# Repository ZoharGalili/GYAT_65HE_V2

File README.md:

# GYAT_65HE_V2
65% hall effect keyboard

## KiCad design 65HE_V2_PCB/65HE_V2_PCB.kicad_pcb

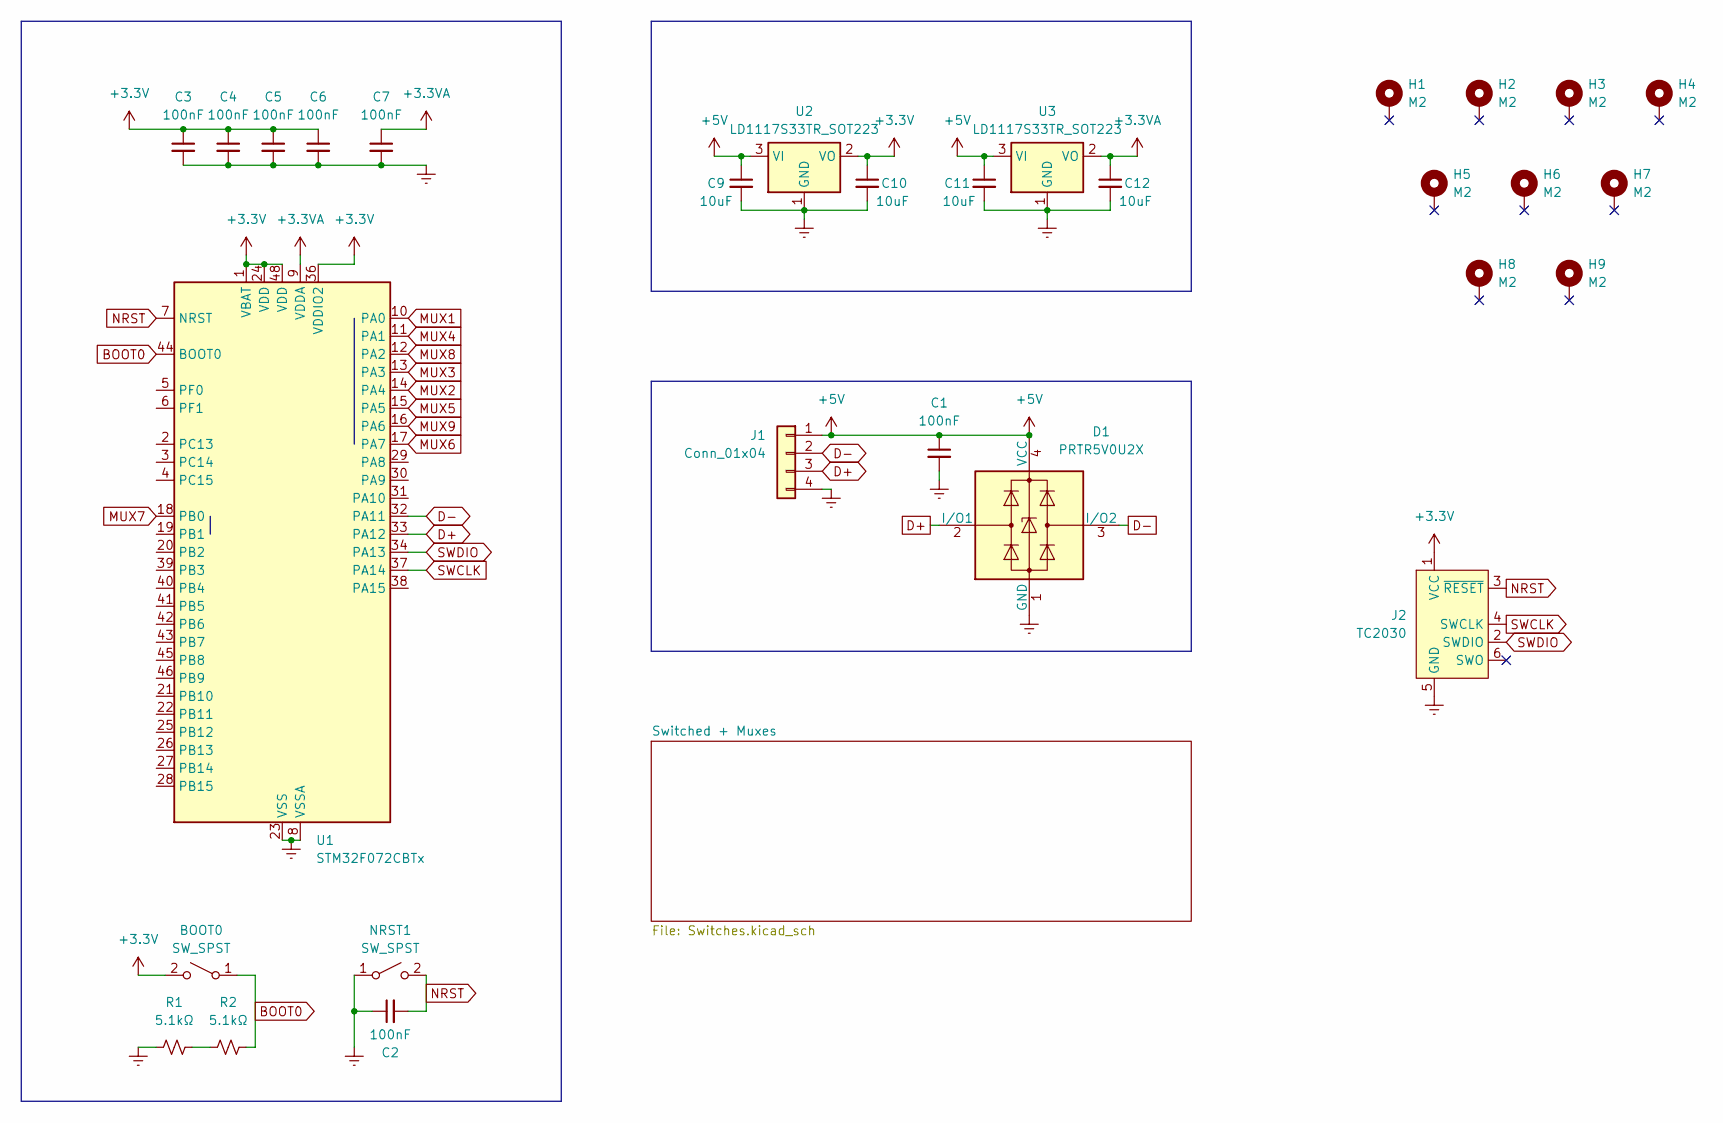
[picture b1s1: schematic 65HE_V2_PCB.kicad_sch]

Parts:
BOOT0: SW_SPST; SW_MSK12C02-HB
C1, C2, C3, C4, C5, C6, C7: 100nF; C_0805_2012Metric
C9, C10, C11, C12: 10uF; C_1206_3216Metric
D1: PRTR5V0U2X; SOT-143
H1, H2, H3, H4, H5, H6, H7, H8, H9: M2; MountingHole_2.2mm_M2_Pad
J1: Conn_01x04; JST_SH_SM04B-SRSS-TB_1x04-1MP_P1.00mm_Horizontal
J2: TC2030; Tag-Connect_TC2030-IDC-FP_2x03_P1.27mm_Vertical
NRST1: SW_SPST; SW_SPST_SKQG_WithStem
R1, R2: 5.1kΩ; R_0805_2012Metric
U1: STM32F072CBTx; LQFP-48_7x7mm_P0.5mm
U2, U3: LD1117S33TR_SOT223; SOT-223-3_TabPin2; LCSC C71121

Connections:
+3.3V: BOOT0.2 (B), C3.1, C4.1, C5.1, C6.1, C10.1, J2.1 (VCC), U1.1 (VBAT), U1.24 (VDD), U1.36 (VDDIO2), U1.48 (VDD), U2.2 (VO); also elsewhere on the board
+3.3VA: C7.1, C12.1, U1.9 (VDDA), U3.2 (VO); also elsewhere on the board
+5V: C1.1, C9.1, C11.1, D1.4 (VCC), J1.1, U2.3 (VI), U3.3 (VI); also elsewhere on the board
BOOT0: BOOT0.1 (A), R2.2, U1.44 (BOOT0); also elsewhere on the board
D+: D1.2 (I/O1), J1.3, U1.33 (PA12); also elsewhere on the board
D-: D1.3 (I/O2), J1.2, U1.32 (PA11); also elsewhere on the board
Earth: C1.2, C2.1, C3.2, C4.2, C5.2, C6.2, C7.2, C9.2, C10.2, C11.2, C12.2, D1.1 (GND), J1.4, J2.5 (GND), NRST1.1 (A), R1.1, U1.8 (VSSA), U1.23 (VSS), U1.35 (VSS), U1.47 (VSS), U2.1 (GND), U3.1 (GND); also elsewhere on the board
MUX1: U1.10 (PA0); also elsewhere on the board
MUX2: U1.14 (PA4); also elsewhere on the board
MUX3: U1.13 (PA3); also elsewhere on the board
MUX4: U1.11 (PA1); also elsewhere on the board
MUX5: U1.15 (PA5); also elsewhere on the board
MUX6: U1.17 (PA7); also elsewhere on the board
MUX7: U1.18 (PB0); also elsewhere on the board
MUX8: U1.12 (PA2); also elsewhere on the board
MUX9: U1.16 (PA6); also elsewhere on the board
NRST: C2.2, J2.3 (~RESET), NRST1.2 (B), U1.7 (NRST); also elsewhere on the board
unnamed: R1.2, R2.1
SWCLK: J2.4 (SWCLK), U1.37 (PA14); also elsewhere on the board
SWDIO: J2.2 (SWDIO), U1.34 (PA13); also elsewhere on the board

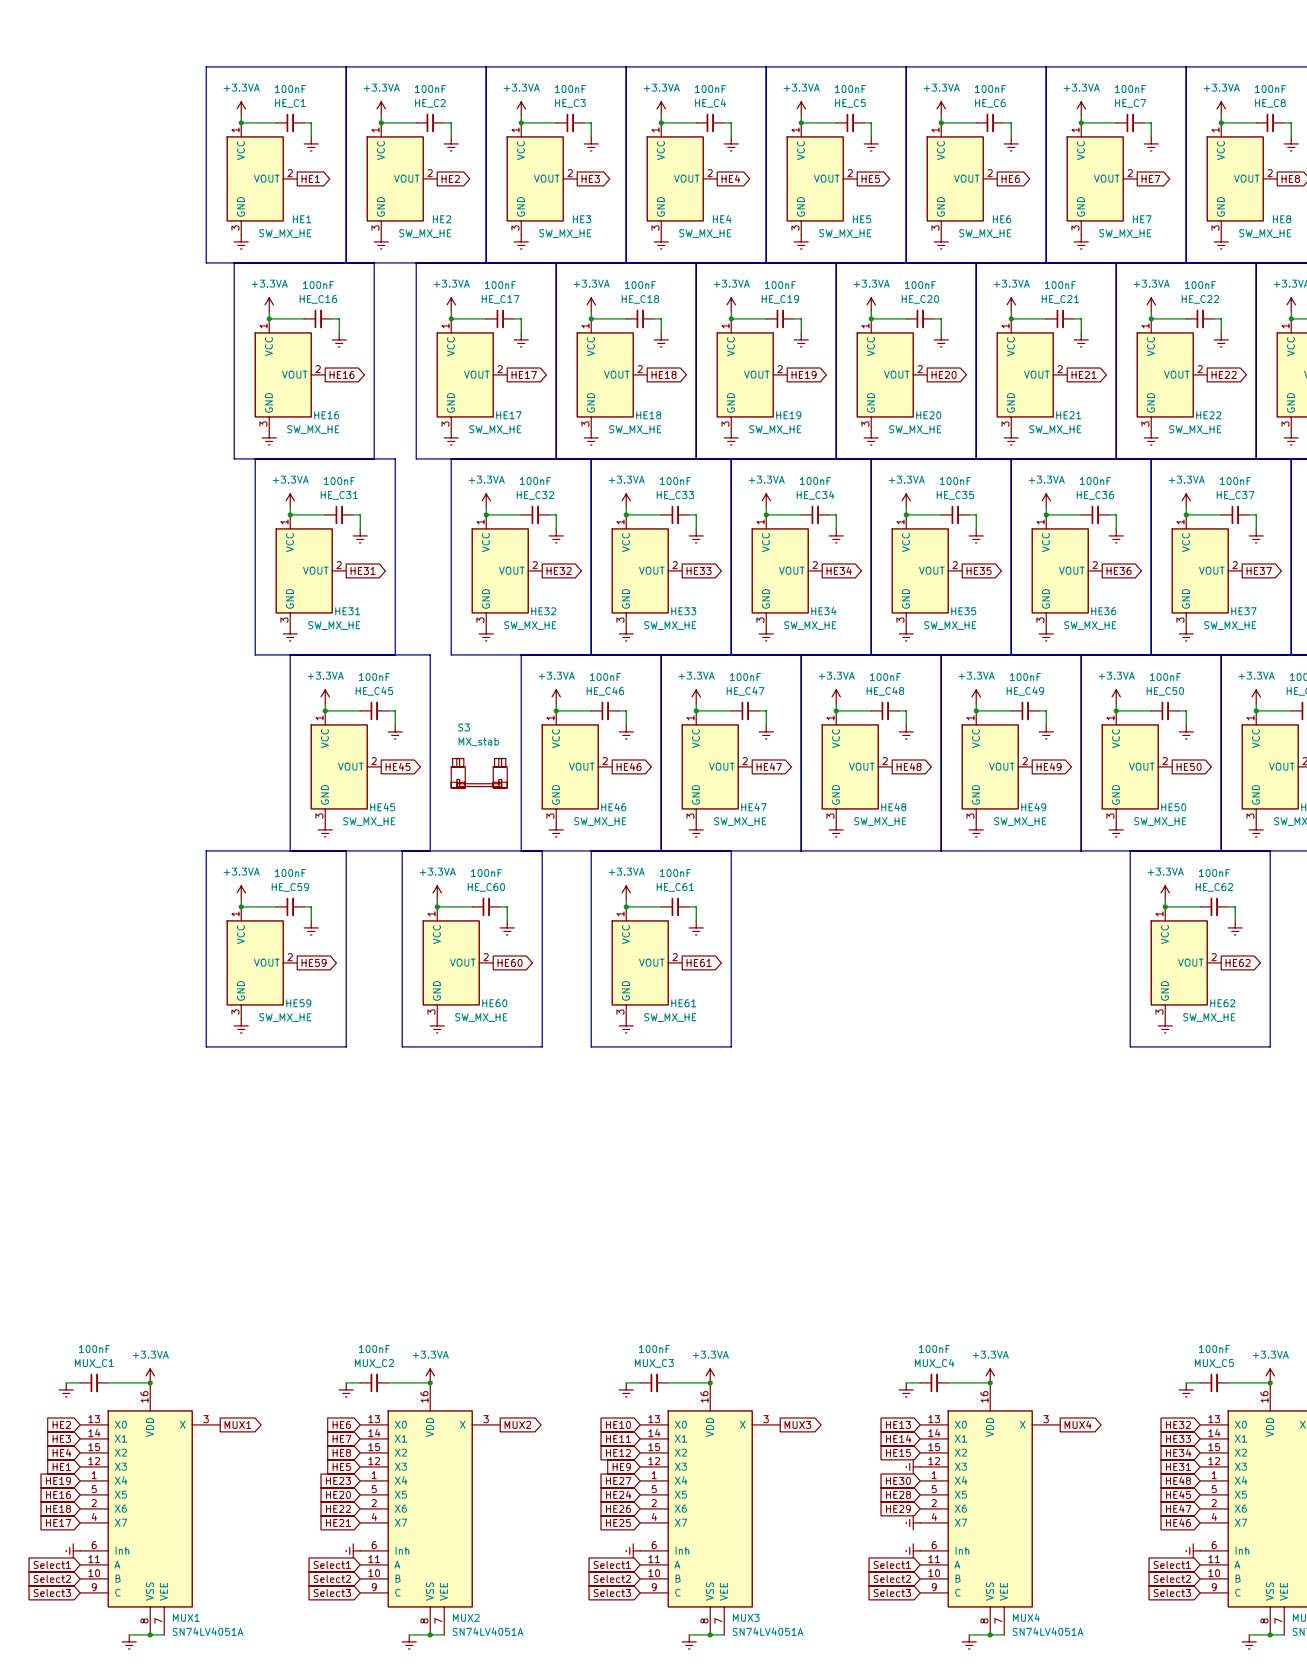
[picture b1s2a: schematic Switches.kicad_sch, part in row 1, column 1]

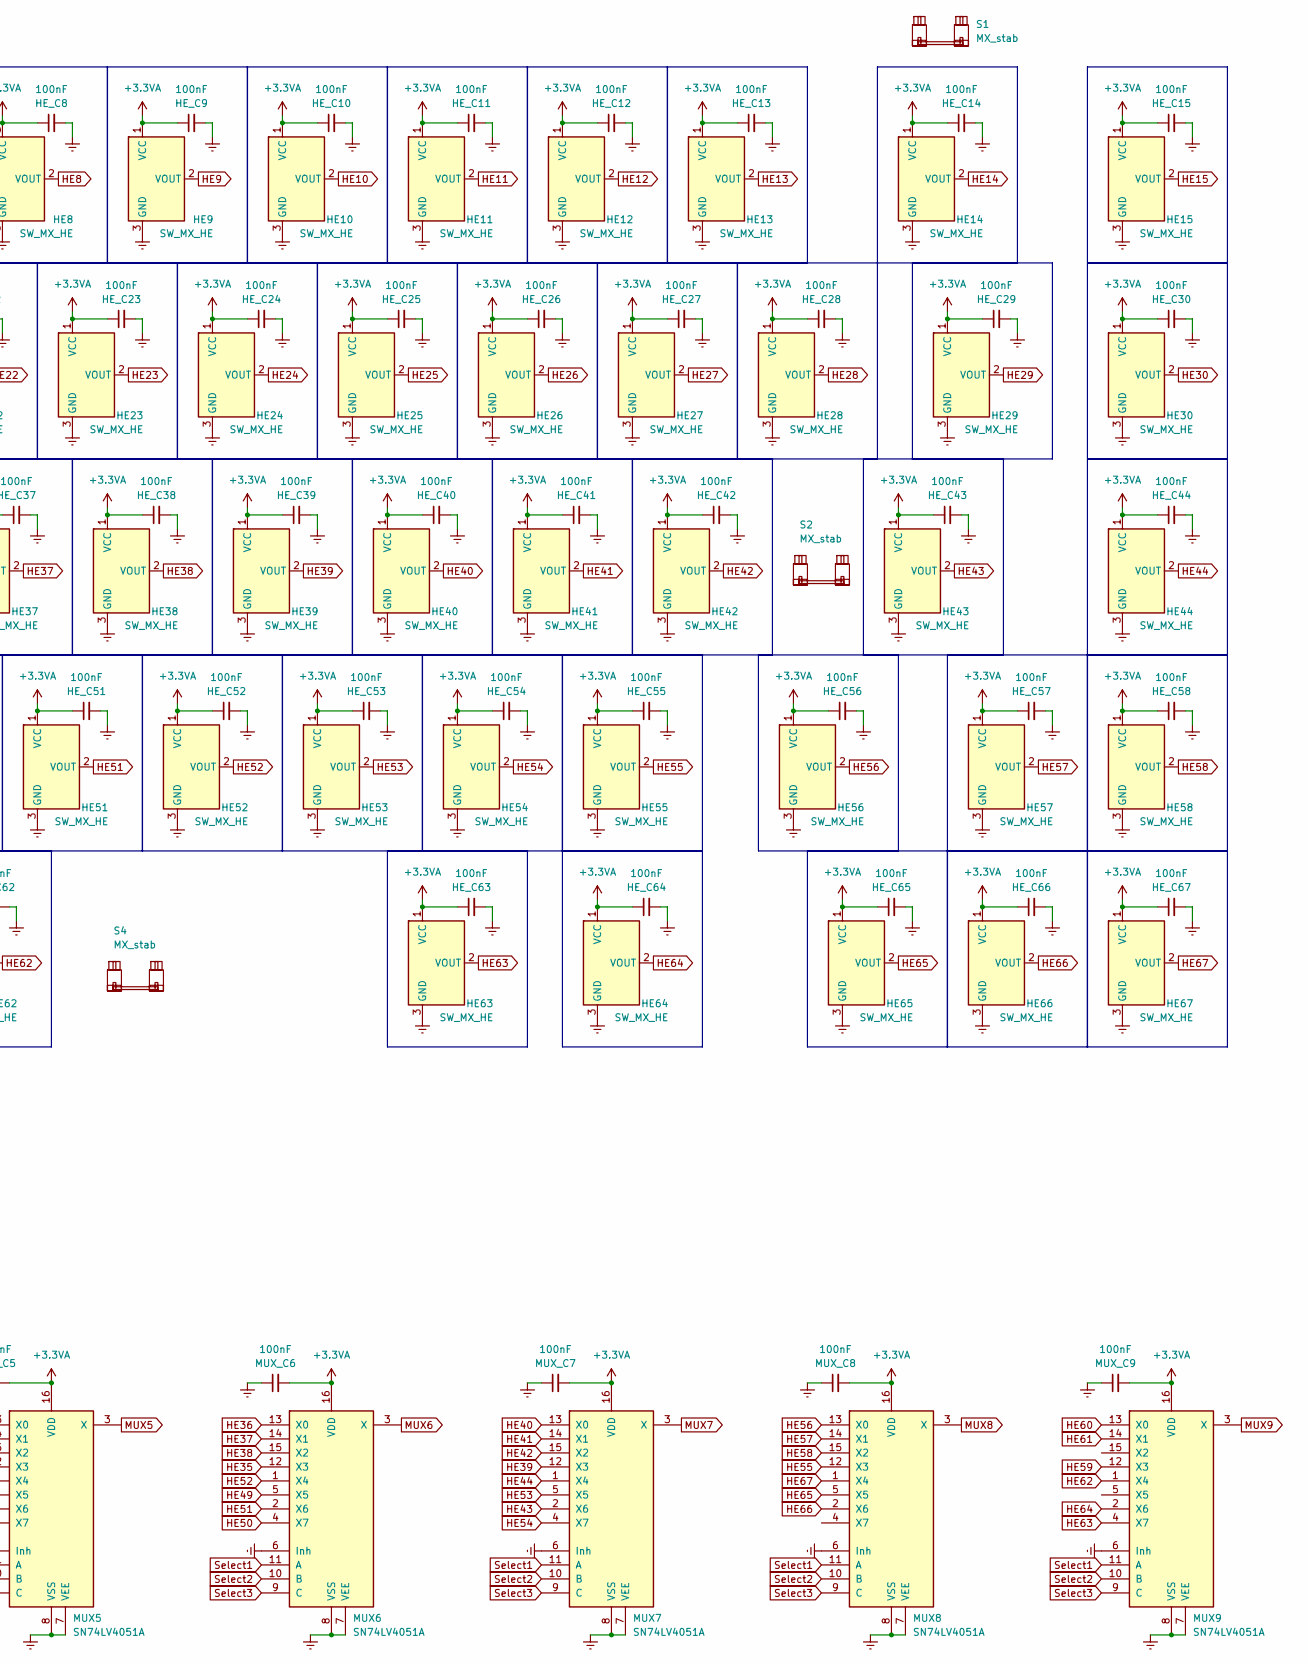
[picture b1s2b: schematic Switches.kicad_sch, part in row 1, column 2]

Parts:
HE1, HE2, HE3, HE4, HE5, HE6, HE7, HE8, HE9, HE10, HE11, HE12, HE13, HE14, HE15, HE16, HE17, HE18, HE19, HE20, HE21, HE22, HE23, HE24, HE25, HE26, HE27, HE28, HE29, HE30, HE31, HE32, HE33, HE34, HE35, HE36, HE37, HE38, HE39, HE40, HE41, HE42, HE43, HE44, HE45, HE46, HE47, HE48, HE49, HE50, HE51, HE52, HE53, HE54, HE55, HE56, HE57, HE58, HE59, HE60, HE61, HE62, HE63, HE64, HE65, HE66, HE67: SW_MX_HE; SW_MX_HE_90deg_1u
HE_C1, HE_C2, HE_C3, HE_C4, HE_C5, HE_C6, HE_C7, HE_C8, HE_C9, HE_C10, HE_C11, HE_C12, HE_C13, HE_C14, HE_C15, HE_C16, HE_C17, HE_C18, HE_C19, HE_C20, HE_C21, HE_C22, HE_C23, HE_C24, HE_C25, HE_C26, HE_C27, HE_C28, HE_C29, HE_C30, HE_C31, HE_C32, HE_C33, HE_C34, HE_C35, HE_C36, HE_C37, HE_C38, HE_C39, HE_C40, HE_C41, HE_C42, HE_C43, HE_C44, HE_C45, HE_C46, HE_C47, HE_C48, HE_C49, HE_C50, HE_C51, HE_C52, HE_C53, HE_C54, HE_C55, HE_C56, HE_C57, HE_C58, HE_C59, HE_C60, HE_C61, HE_C62, HE_C63, HE_C64, HE_C65, HE_C66, HE_C67: 100nF; C_0805_2012Metric
MUX1, MUX2, MUX3, MUX4, MUX5, MUX6, MUX7, MUX8, MUX9: SN74LV4051A; TSSOP-16_4.4x5mm_P0.65mm
MUX_C1, MUX_C2, MUX_C3, MUX_C4, MUX_C5, MUX_C6, MUX_C7, MUX_C8, MUX_C9: 100nF; C_0805_2012Metric
S1: MX_stab; STAB_MX_2u
S2, S3: MX_stab; STAB_MX_2.25u
S4: MX_stab; STAB_MX_6.25u

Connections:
+3.3VA: HE1.1 (VCC), HE2.1 (VCC), HE3.1 (VCC), HE4.1 (VCC), HE5.1 (VCC), HE6.1 (VCC), HE7.1 (VCC), HE8.1 (VCC), HE9.1 (VCC), HE10.1 (VCC), HE11.1 (VCC), HE12.1 (VCC), HE13.1 (VCC), HE14.1 (VCC), HE15.1 (VCC), HE16.1 (VCC), HE17.1 (VCC), HE18.1 (VCC), HE19.1 (VCC), HE20.1 (VCC), HE21.1 (VCC), HE22.1 (VCC), HE23.1 (VCC), HE24.1 (VCC), HE25.1 (VCC), HE26.1 (VCC), HE27.1 (VCC), HE28.1 (VCC), HE29.1 (VCC), HE30.1 (VCC), HE31.1 (VCC), HE32.1 (VCC), HE33.1 (VCC), HE34.1 (VCC), HE35.1 (VCC), HE36.1 (VCC), HE37.1 (VCC), HE38.1 (VCC), HE39.1 (VCC), HE40.1 (VCC), HE41.1 (VCC), HE42.1 (VCC), HE43.1 (VCC), HE44.1 (VCC), HE45.1 (VCC), HE46.1 (VCC), HE47.1 (VCC), HE48.1 (VCC), HE49.1 (VCC), HE50.1 (VCC), HE51.1 (VCC), HE52.1 (VCC), HE53.1 (VCC), HE54.1 (VCC), HE55.1 (VCC), HE56.1 (VCC), HE57.1 (VCC), HE58.1 (VCC), HE59.1 (VCC), HE60.1 (VCC), HE61.1 (VCC), HE62.1 (VCC), HE63.1 (VCC), HE64.1 (VCC), HE65.1 (VCC), HE66.1 (VCC), HE67.1 (VCC), HE_C1.1, HE_C2.1, HE_C3.1, HE_C4.1, HE_C5.1, HE_C6.1, HE_C7.1, HE_C8.1, HE_C9.1, HE_C10.1, HE_C11.1, HE_C12.1, HE_C13.1, HE_C14.1, HE_C15.1, HE_C16.1, HE_C17.1, HE_C18.1, HE_C19.1, HE_C20.1, HE_C21.1, HE_C22.1, HE_C23.1, HE_C24.1, HE_C25.1, HE_C26.1, HE_C27.1, HE_C28.1, HE_C29.1, HE_C30.1, HE_C31.1, HE_C32.1, HE_C33.1, HE_C34.1, HE_C35.1, HE_C36.1, HE_C37.1, HE_C38.1, HE_C39.1, HE_C40.1, HE_C41.1, HE_C42.1, HE_C43.1, HE_C44.1, HE_C45.1, HE_C46.1, HE_C47.1, HE_C48.1, HE_C49.1, HE_C50.1, HE_C51.1, HE_C52.1, HE_C53.1, HE_C54.1, HE_C55.1, HE_C56.1, HE_C57.1, HE_C58.1, HE_C59.1, HE_C60.1, HE_C61.1, HE_C62.1, HE_C63.1, HE_C64.1, HE_C65.1, HE_C66.1, HE_C67.1, MUX1.16 (VDD), MUX2.16 (VDD), MUX3.16 (VDD), MUX4.16 (VDD), MUX5.16 (VDD), MUX6.16 (VDD), MUX7.16 (VDD), MUX8.16 (VDD), MUX9.16 (VDD), MUX_C1.2, MUX_C2.2, MUX_C3.2, MUX_C4.2, MUX_C5.2, MUX_C6.2, MUX_C7.2, MUX_C8.2, MUX_C9.2; also elsewhere on the board
Earth: HE1.3 (GND), HE2.3 (GND), HE3.3 (GND), HE4.3 (GND), HE5.3 (GND), HE6.3 (GND), HE7.3 (GND), HE8.3 (GND), HE9.3 (GND), HE10.3 (GND), HE11.3 (GND), HE12.3 (GND), HE13.3 (GND), HE14.3 (GND), HE15.3 (GND), HE16.3 (GND), HE17.3 (GND), HE18.3 (GND), HE19.3 (GND), HE20.3 (GND), HE21.3 (GND), HE22.3 (GND), HE23.3 (GND), HE24.3 (GND), HE25.3 (GND), HE26.3 (GND), HE27.3 (GND), HE28.3 (GND), HE29.3 (GND), HE30.3 (GND), HE31.3 (GND), HE32.3 (GND), HE33.3 (GND), HE34.3 (GND), HE35.3 (GND), HE36.3 (GND), HE37.3 (GND), HE38.3 (GND), HE39.3 (GND), HE40.3 (GND), HE41.3 (GND), HE42.3 (GND), HE43.3 (GND), HE44.3 (GND), HE45.3 (GND), HE46.3 (GND), HE47.3 (GND), HE48.3 (GND), HE49.3 (GND), HE50.3 (GND), HE51.3 (GND), HE52.3 (GND), HE53.3 (GND), HE54.3 (GND), HE55.3 (GND), HE56.3 (GND), HE57.3 (GND), HE58.3 (GND), HE59.3 (GND), HE60.3 (GND), HE61.3 (GND), HE62.3 (GND), HE63.3 (GND), HE64.3 (GND), HE65.3 (GND), HE66.3 (GND), HE67.3 (GND), HE_C1.2, HE_C2.2, HE_C3.2, HE_C4.2, HE_C5.2, HE_C6.2, HE_C7.2, HE_C8.2, HE_C9.2, HE_C10.2, HE_C11.2, HE_C12.2, HE_C13.2, HE_C14.2, HE_C15.2, HE_C16.2, HE_C17.2, HE_C18.2, HE_C19.2, HE_C20.2, HE_C21.2, HE_C22.2, HE_C23.2, HE_C24.2, HE_C25.2, HE_C26.2, HE_C27.2, HE_C28.2, HE_C29.2, HE_C30.2, HE_C31.2, HE_C32.2, HE_C33.2, HE_C34.2, HE_C35.2, HE_C36.2, HE_C37.2, HE_C38.2, HE_C39.2, HE_C40.2, HE_C41.2, HE_C42.2, HE_C43.2, HE_C44.2, HE_C45.2, HE_C46.2, HE_C47.2, HE_C48.2, HE_C49.2, HE_C50.2, HE_C51.2, HE_C52.2, HE_C53.2, HE_C54.2, HE_C55.2, HE_C56.2, HE_C57.2, HE_C58.2, HE_C59.2, HE_C60.2, HE_C61.2, HE_C62.2, HE_C63.2, HE_C64.2, HE_C65.2, HE_C66.2, HE_C67.2, MUX1.6 (Inh), MUX1.7 (VEE), MUX1.8 (VSS), MUX2.6 (Inh), MUX2.7 (VEE), MUX2.8 (VSS), MUX3.6 (Inh), MUX3.7 (VEE), MUX3.8 (VSS), MUX4.4 (X7), MUX4.6 (Inh), MUX4.7 (VEE), MUX4.8 (VSS), MUX4.12 (X3), MUX5.6 (Inh), MUX5.7 (VEE), MUX5.8 (VSS), MUX6.6 (Inh), MUX6.7 (VEE), MUX6.8 (VSS), MUX7.6 (Inh), MUX7.7 (VEE), MUX7.8 (VSS), MUX8.6 (Inh), MUX8.7 (VEE), MUX8.8 (VSS), MUX9.6 (Inh), MUX9.7 (VEE), MUX9.8 (VSS), MUX_C1.1, MUX_C2.1, MUX_C3.1, MUX_C4.1, MUX_C5.1, MUX_C6.1, MUX_C7.1, MUX_C8.1, MUX_C9.1; also elsewhere on the board
HE1: HE1.2 (VOUT), MUX1.12 (X3)
HE2: HE2.2 (VOUT), MUX1.13 (X0)
HE3: HE3.2 (VOUT), MUX1.14 (X1)
HE4: HE4.2 (VOUT), MUX1.15 (X2)
HE5: HE5.2 (VOUT), MUX2.12 (X3)
HE6: HE6.2 (VOUT), MUX2.13 (X0)
HE7: HE7.2 (VOUT), MUX2.14 (X1)
HE8: HE8.2 (VOUT), MUX2.15 (X2)
HE9: HE9.2 (VOUT), MUX3.12 (X3)
HE10: HE10.2 (VOUT), MUX3.13 (X0)
HE11: HE11.2 (VOUT), MUX3.14 (X1)
HE12: HE12.2 (VOUT), MUX3.15 (X2)
HE13: HE13.2 (VOUT), MUX4.13 (X0)
HE14: HE14.2 (VOUT), MUX4.14 (X1)
HE15: HE15.2 (VOUT), MUX4.15 (X2)
HE16: HE16.2 (VOUT), MUX1.5 (X5)
HE17: HE17.2 (VOUT), MUX1.4 (X7)
HE18: HE18.2 (VOUT), MUX1.2 (X6)
HE19: HE19.2 (VOUT), MUX1.1 (X4)
HE20: HE20.2 (VOUT), MUX2.5 (X5)
HE21: HE21.2 (VOUT), MUX2.4 (X7)
HE22: HE22.2 (VOUT), MUX2.2 (X6)
HE23: HE23.2 (VOUT), MUX2.1 (X4)
HE24: HE24.2 (VOUT), MUX3.5 (X5)
HE25: HE25.2 (VOUT), MUX3.4 (X7)
HE26: HE26.2 (VOUT), MUX3.2 (X6)
HE27: HE27.2 (VOUT), MUX3.1 (X4)
HE28: HE28.2 (VOUT), MUX4.5 (X5)
HE29: HE29.2 (VOUT), MUX4.2 (X6)
HE30: HE30.2 (VOUT), MUX4.1 (X4)
HE31: HE31.2 (VOUT), MUX5.12 (X3)
HE32: HE32.2 (VOUT), MUX5.13 (X0)
HE33: HE33.2 (VOUT), MUX5.14 (X1)
HE34: HE34.2 (VOUT), MUX5.15 (X2)
HE35: HE35.2 (VOUT), MUX6.12 (X3)
HE36: HE36.2 (VOUT), MUX6.13 (X0)
HE37: HE37.2 (VOUT), MUX6.14 (X1)
HE38: HE38.2 (VOUT), MUX6.15 (X2)
HE39: HE39.2 (VOUT), MUX7.12 (X3)
HE40: HE40.2 (VOUT), MUX7.13 (X0)
HE41: HE41.2 (VOUT), MUX7.14 (X1)
HE42: HE42.2 (VOUT), MUX7.15 (X2)
HE43: HE43.2 (VOUT), MUX7.2 (X6)
HE44: HE44.2 (VOUT), MUX7.1 (X4)
HE45: HE45.2 (VOUT), MUX5.5 (X5)
HE46: HE46.2 (VOUT), MUX5.4 (X7)
HE47: HE47.2 (VOUT), MUX5.2 (X6)
HE48: HE48.2 (VOUT), MUX5.1 (X4)
HE49: HE49.2 (VOUT), MUX6.5 (X5)
HE50: HE50.2 (VOUT), MUX6.4 (X7)
HE51: HE51.2 (VOUT), MUX6.2 (X6)
HE52: HE52.2 (VOUT), MUX6.1 (X4)
HE53: HE53.2 (VOUT), MUX7.5 (X5)
HE54: HE54.2 (VOUT), MUX7.4 (X7)
HE55: HE55.2 (VOUT), MUX8.12 (X3)
HE56: HE56.2 (VOUT), MUX8.13 (X0)
HE57: HE57.2 (VOUT), MUX8.14 (X1)
HE58: HE58.2 (VOUT), MUX8.15 (X2)
HE59: HE59.2 (VOUT), MUX9.12 (X3)
HE60: HE60.2 (VOUT), MUX9.13 (X0)
HE61: HE61.2 (VOUT), MUX9.14 (X1)
HE62: HE62.2 (VOUT), MUX9.1 (X4)
HE63: HE63.2 (VOUT), MUX9.4 (X7)
HE64: HE64.2 (VOUT), MUX9.2 (X6)
HE65: HE65.2 (VOUT), MUX8.5 (X5)
HE66: HE66.2 (VOUT), MUX8.2 (X6)
HE67: HE67.2 (VOUT), MUX8.1 (X4)
MUX1: MUX1.3 (X); also elsewhere on the board
MUX2: MUX2.3 (X); also elsewhere on the board
MUX3: MUX3.3 (X); also elsewhere on the board
MUX4: MUX4.3 (X); also elsewhere on the board
MUX5: MUX5.3 (X); also elsewhere on the board
MUX6: MUX6.3 (X); also elsewhere on the board
MUX7: MUX7.3 (X); also elsewhere on the board
MUX8: MUX8.3 (X); also elsewhere on the board
MUX9: MUX9.3 (X); also elsewhere on the board
Select1: MUX1.11 (A), MUX2.11 (A), MUX3.11 (A), MUX4.11 (A), MUX5.11 (A), MUX6.11 (A), MUX7.11 (A), MUX8.11 (A), MUX9.11 (A)
Select2: MUX1.10 (B), MUX2.10 (B), MUX3.10 (B), MUX4.10 (B), MUX5.10 (B), MUX6.10 (B), MUX7.10 (B), MUX8.10 (B), MUX9.10 (B)
Select3: MUX1.9 (C), MUX2.9 (C), MUX3.9 (C), MUX4.9 (C), MUX5.9 (C), MUX6.9 (C), MUX7.9 (C), MUX8.9 (C), MUX9.9 (C)

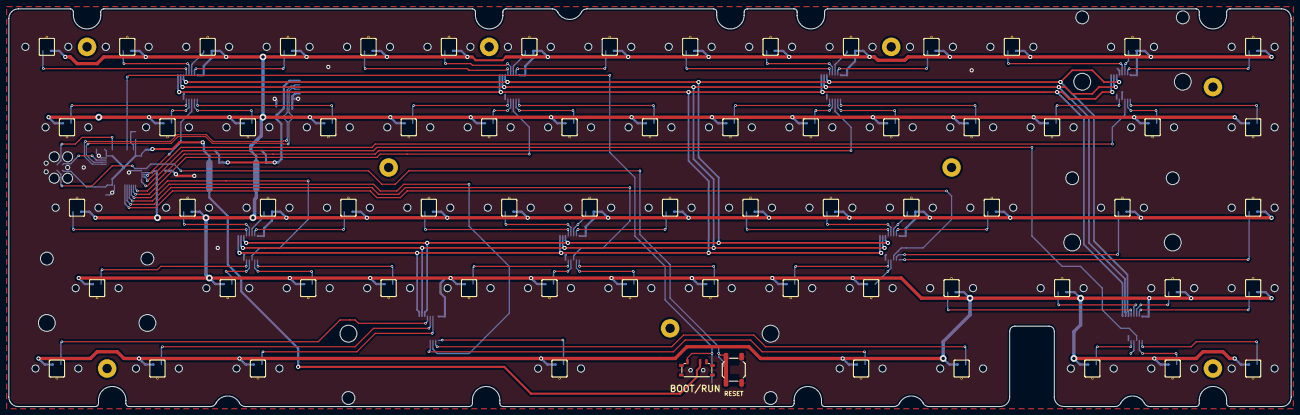
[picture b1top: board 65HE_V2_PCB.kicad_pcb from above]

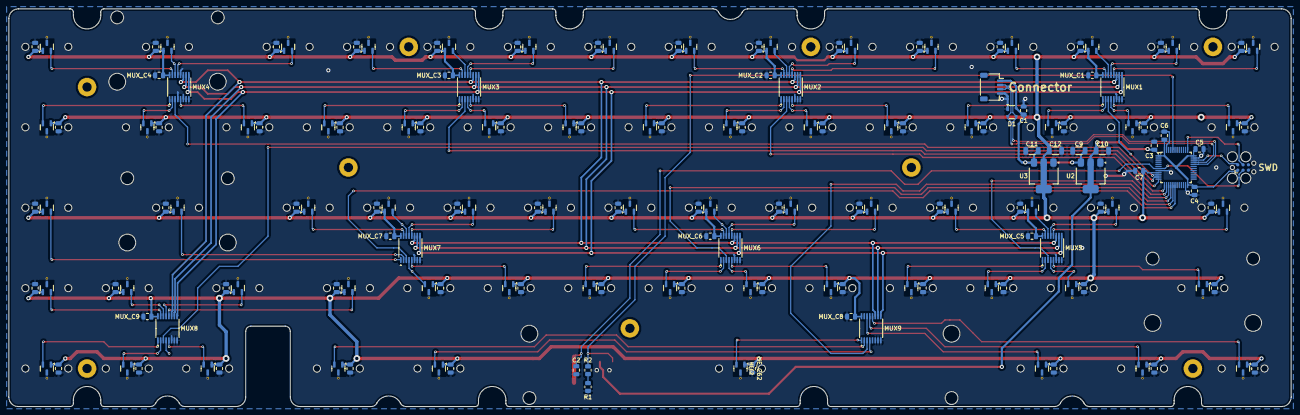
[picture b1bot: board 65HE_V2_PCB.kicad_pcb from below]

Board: 2 copper layers, 303.8 x 94.2 mm, 186 parts (171 on the bottom side), 90 nets.

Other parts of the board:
BOOT/RUN: SW_SPST; SW_MSK12C02-HB
Connector: Conn_01x04; JST_SH_SM04B-SRSS-TB_1x04-1MP_P1.00mm_Horizontal
RESET: SW_SPST; SW_SPST_SKQG_WithStem
SWD: TC2030; Tag-Connect_TC2030-IDC-FP_2x03_P1.27mm_Vertical

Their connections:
+3.3V: BOOT/RUN.2 (B), SWD.1 (VCC); also elsewhere on the board
+5V: Connector.1; also elsewhere on the board
BOOT0: BOOT/RUN.1 (A); also elsewhere on the board
D+: Connector.3; also elsewhere on the board
D-: Connector.2; also elsewhere on the board
Earth: Connector.4, RESET.1 (A), SWD.5 (GND); also elsewhere on the board
NRST: RESET.2 (B), SWD.3 (~RESET); also elsewhere on the board
SWCLK: SWD.4 (SWCLK); also elsewhere on the board
SWDIO: SWD.2 (SWDIO); also elsewhere on the board

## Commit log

2025-06-10 initial commit?
2025-06-10 placed switches and muxes
2025-06-10 Vega + Bakeneko Board Outline
2025-06-10 holes for standoffs
2025-06-10 wired all the switched
2025-06-14 pcb done?
